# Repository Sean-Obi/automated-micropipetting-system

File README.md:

# Automated Micropipetting System - Gantry + Linear Actuator + Touchscreen

A low-cost, bench-top pipetting robot that lets users with tremors, fatigue or limited upper-limb mobility pipette independently. A modified Ender-3 gantry positions an actuator-driven 3D-printed micropipette over labware, and the whole run is set up from a Nextion touchscreen: pick a source, the destination wells and a volume, then press start.

Built as the Design & Prototyping group project built by nine second-year Molecular Bioengineering students at Imperial College London, supervised by Dr Ian Radcliffe.

> ❗️**Prototype, not a certified lab instrument.** Accuracy was validated on the bench only. Don't use it for regulated or clinical work.

---

## Features
- **3-axis Cartesian gantry** built on a Creality Ender-3 frame, with A4988 drivers and end-stop homing on every axis.
- **Coordinated XY motion** using Bresenham-style interpolation, so both axes arrive together. Z always retracts to a safe height before any travel.
- **Actuator-driven pipette.** A 12 V linear actuator presses the plunger of an open-source, ISO 8655-compliant 3D-printed micropipette.
- **Touchscreen workflow.** Source → wells → volume → start on a 4.3" Nextion HMI, with input validation done on the display.
- **Tactile keypad** (4×3) as an alternative input, plus a **buzzer** for audio feedback at the start and end of each job.
- **Modular PLA base** with a 5×8 tube rack and two beaker slots in fixed, grooved positions.
- **£483.53** material cost, against more than £35,000 for commercial liquid handlers.

---

## Hardware
- Elegoo Mega 2560 R3 (Arduino Mega compatible)
- Creality Ender-3 3D printer (frame, rails, NEMA17 steppers, end-stops, PSU)
- 3 × A4988 stepper driver modules
- Actuonix Linear Actuator Control (LAC) board + linear actuator
- 3D-printed adjustable micropipette (3 mL syringe) + custom pipette/actuator holder
- Nextion NX4827T043 4.3" HMI touchscreen + microSD card
- 4×3 membrane keypad, piezo buzzer
- 3 × LM2596 buck converters, custom interface PCB

Full part list with suppliers and prices: [`hardware/BOM.csv`](hardware/BOM.csv).

### Interface PCB
A 2-layer, 132 × 80 mm board that carries the three A4988 drivers, power inputs and all device connectors, with a 2×14 header to the Mega. KiCad files and Gerbers are in [`hardware/`](hardware/).

> The layout in this repo is a 2026 reconstruction from the report schematic, not the original files sent to JLCPCB. See [`hardware/README.md`](hardware/README.md#board-layout).

### Power
- Mains supplies the Ender-3 PSU (24 W total draw).
- **12 V rail** (via buck converter) powers the LAC board and actuator.
- **5 V rail** (via buck converters) powers the Mega, the A4988 logic and the Nextion.
- A separate buck converter supplies the stepper motor voltage (VMOT).

> Set every LM2596 output with a multimeter **before** connecting anything. They ship at arbitrary voltages.

---

## Pinout / Wiring

| Component | Signal | Mega Pin |
|---|---|---|
| X axis | STEP / DIR / End-stop | **6** / **7** / **5** |
| Y axis | STEP / DIR / End-stop | **9** / **10** / **8** |
| Z axis | STEP / DIR / End-stop | **12** / **13** / **11** |
| LAC board | VC (position signal) | **4** (via R2, with R1 pull-up) |
| Nextion | RX / TX | **TX1 (18)** / **RX1 (19)** |
| Keypad | Rows / columns | **22, 24, 26, 28, 30, 32, 34** |
| Buzzer | + | **2** |
| A4988 | VDD / VMOT | 5V / motor buck output |
| A4988 | SLP ↔ RST | Tied together |
| End-stops | Switch → GND | `INPUT_PULLUP`, triggered = `HIGH` |

> Note: the report's schematic figure shows DIR/STEP swapped, the buzzer on D52 and the Nextion on TX0/RX0. The table above follows the firmware, which is what actually ran. Full schematic: [`hardware/pcb_design.kicad_sch`](hardware/pcb_design.kicad_sch).

---

## Software Requirements
Arduino IDE 1.8+ or Arduino IDE 2.x. **No external libraries** are needed. The sketch only uses the Arduino core (`Serial`, `Serial1`, `tone()`).

For the touchscreen:
- **Nextion Editor** to edit the `.HMI` and compile the `.tft`.

---

## Installation
1. **Clone the repository**
   ```bash
   git clone https://github.com/your-username/automated-micropipetting-system.git
   cd automated-micropipetting-system
   ```
2. Wire the system per the pin table above, and set the A4988 current limits and buck converter voltages.
3. Open `firmware/pipetting_controller/pipetting_controller.ino` in the Arduino IDE.
4. Select **Board → Arduino Mega or Mega 2560** and the correct port.
5. **Verify/Compile**, then **Upload**.
6. Copy the Nextion `.tft` to a FAT32 microSD card, insert it into the display and power it on to flash.
7. (Optional) Open **Tools → Serial Monitor** at **9600 baud** to watch the job logs.

---

## Configuration

Edit these constants near the top of the sketch. All positions are in **steps from home**:

```cpp
const long Z_SAFE_HEIGHT = 1700;   // travel height between positions
const long Z_WORK_HEIGHT = 300;    // tip-in-liquid height
unsigned long stepDelayXY = 1500;  // µs, XY step half-period (lower = faster)
unsigned long stepDelayZ  = 1200;  // µs, Z step half-period
const long MAX_HOMING_STEPS_Z = MAX_BACKWARD_Z + 100;  // Z homing timeout
```

Labware positions come from calibration and must be re-measured if the base changes:
```cpp
Coord wells[]   = { { 890, 500 }, { 940, 500 }, ... };  // 5×8 rack, 50-step pitch
Coord beakers[] = { { 400, 700 }, { 670, 700 } };       // left, right
```

Step resolution (from calibration):
- **X:** ~0.199 mm/step
- **Y:** ~0.205 mm/step
- **Z:** 0.04 mm/step

---

## How It Works

1. **Homing**  
   At power-up, each axis drives toward its end-stop (X → Y → Z) to set an absolute zero. Z then rises to `Z_SAFE_HEIGHT`.

2. **Job Entry**  
   The user steps through the Nextion screens (source type → beaker or input well → output wells → volume). The display checks the inputs, then sends a single packet over `Serial1`, terminated by `#`.

3. **Packet Parsing**  
   `parsePacket()` decodes the ASCII fields (`I=` input well, `O=` output wells) and the 4-byte little-endian fields (`V=` volume, `B=` beaker side, `T=` source type), then plays a confirmation beep.

4. **Execution**  
   The gantry travels to the source and then to each output well in turn. At every stop, `holdZatWorkHeight()` lowers the tip, dwells for 3 s, then retracts. Z always returns to safe height before any XY move.

5. **Return**  
   The head goes back to (0, 0), the end melody plays, and the buffer clears ready for the next job.

---

## Usage

1. Plug in the system and wait for homing to finish.
2. Fill the source beaker or tubes and place them in the marked slots. Fit a fresh tip.
3. On the touchscreen, choose **Beaker** or **Tubes**, then pick the source.
4. Tap the output wells and press **Confirm**.
5. Enter the volume in µL and tap **Start Pipetting**.
6. Two beeps confirm the job, and a melody plays when the head is back home.
7. Remove the tip by hand. There is no auto-eject yet.

Full walkthrough with screenshots: [`docs/user-guide.md`](docs/user-guide.md).

---

## Data Output

### Serial Monitor (9600)
```
Ready to receive Nextion packets...
Input Well: 0
Output Wells: 12,13,14,
Volume: 74
Beaker Side: 1
Source Type: 1
```

### Nextion Packet Format
```
T=<4B> B=<4B> I=<digits> O=<d>,<d>,...; V=<4B> #
```
| Field | Meaning |
|---|---|
| `T` | Source type: 1 = beaker, 2 = tubes |
| `B` | Beaker side: 1 = left, 2 = right |
| `I` | Input well index (0–39) |
| `O` | Output well indices, `;`-terminated |
| `V` | Volume in µL |

### Debug Commands (USB Serial)
| Command | Action |
|---|---|
| `X0` | Re-home X |
| `Y0` | Re-home Y |
| `Z0` | Re-home Z |

---

## Results

- **Volume accuracy:** the pipette alone was calibrated to within ±1% of target. The actuator adds extra uncertainty at system level, and accuracy drops at low volumes.
- **Cross-contamination:** no visible carryover in dye-then-clear runs with tip changes. This was checked by eye only.
- **Gantry:** the step-to-distance response is linear on all axes ([calibration](docs/calibration.md)).
- **User testing (n = 20):**
  - 90% rated lab fit 4–5/5.
  - 75% needed minimal or no instructions.
  - The top requests were a bigger screen, larger touch targets and tactile buttons.

Full evaluation: [`docs/testing.md`](docs/testing.md).

---

## Troubleshooting

- **An axis runs into the frame during homing**
  - Check the end-stop wiring and that it reads `HIGH` when pressed (`LIMIT_PRESSED = HIGH`).
  - XY homing has no step limit. Cut power or press reset if a switch fails.

- **The touchscreen does nothing when you press Start**
  - Nextion TX must go to Mega **RX1 (19)** and Nextion RX to **TX1 (18)**. The crossover matters.
  - Both sides need to be at **9600 baud**.
  - Check that the packet ends with `#`. Watch the Serial Monitor for the `Input Well:` lines.

- **The tip misses the wells**
  - Re-home with `X0` / `Y0` / `Z0`. Position isn't re-homed between jobs, so lost steps accumulate.
  - Re-measure `wells[]` / `beakers[]` if the base has moved.

- **A motor stutters, skips or runs hot**
  - Re-set the A4988 current limit on the trim pot.
  - Increase `stepDelayXY` / `stepDelayZ` to slow the motion.
  - Check that VMOT is present and the driver has airflow or a heatsink.

- **A motor runs backwards**
  - Swap one coil pair (1A/1B) on that driver.

- **The tip doesn't reach the liquid, or it crashes into the tube bottom**
  - Adjust `Z_WORK_HEIGHT`.

---

## Notes & Limitations
- **The volume isn't used by the firmware yet.** `V=` is parsed and logged, but this sketch doesn't generate the actuator PWM. Actuation happens outside this file.
- **16-bit `int` on AVR.** The 4-byte field decoding shifts by 16 and 24 bits, which overflows a 16-bit `int`. It works only because the upper bytes are zero. It should use `int32_t`.
- **Everything is blocking.** There's no cancel or emergency stop mid-job.
- **The keypad isn't implemented here.** It is wired, but this sketch doesn't read it.
- **Tips are ejected manually.** Servo-driven ejection and a tip bin are on the roadmap.
- **Materials.** PLA parts suit prototyping only. The pipette–carriage joint needs a stiffer mount.
- **The volume range is inconsistent across sources.** The spec says 100–1000 µL, the UI guide 10–100 µL, and testing covered 30–100 µL.

More detail: [`firmware/README.md`](firmware/README.md#known-issues).

---

## Project Structure

```
automated-micropipetting-system/
├── firmware/
│   ├── pipetting_controller/
│   │   └── pipetting_controller.ino   # Gantry, homing, Nextion packet parser
│   └── README.md                      # Pinout, protocol, known issues
├── hardware/
│   ├── pcb_design.kicad_pro           # KiCad project
│   ├── pcb_design.kicad_sch           # Schematic
│   ├── pcb_design.kicad_pcb           # Board layout (reconstructed)
│   ├── pcb_design_gerbers.zip         # Gerbers + drill files
│   ├── apms.pretty/                   # Project footprint library
│   ├── pcb_design.pdf                 # Plotted schematic
│   ├── schematic.png                  # Original figure from the report
│   ├── BOM.csv                        # Bill of materials (£483.53)
│   ├── tools/                         # Schematic + board generation scripts
│   └── README.md                      # Power rails, drivers, wiring
├── hmi/
│   └── README.md                      # Nextion screen flow
├── cad/
│   └── README.md                      # SolidWorks parts (base, holders)
├── docs/
│   ├── images/                        # Figures
│   ├── calibration.md                 # Gantry step calibration
│   ├── testing.md                     # Accuracy, contamination, user testing
│   ├── user-guide.md                  # Operating instructions
│   └── final-report.pdf               # Full project report
└── README.md
```

---

## Team
Ben Jones · Jenna du Preez · Kailin Wang · Leonardo Grimaldi · **Sean Obi** · Sheena Ling · Sumaiyah Zaman · Tayeb Tadlaoui · Yasmine Marenzi

### My Contributions (Sean Obi)
- **PCB design.** Designed the custom interface PCB (schematic and layout), manufactured by JLCPCB.
- **Electronics lead.** System wiring and power distribution (12 V actuator rail, 5 V logic), and integration of the drivers, LAC board, keypad, display and buzzer.
- **Firmware.** Co-developed the Arduino controller: homing, XY motion and Nextion packet handling.
- **Gantry.** Assembled the Ender-3 conversion.
- **User testing.** Coordinated the n = 20 study.
- **Final report.** Co-authored it.

---

## Acknowledgements
- Dr Ian Radcliffe (supervisor)
- Imperial Disability Advisory Services and Dr Katherine Dean
- Ms Iris Latham (disability consultant) and Dr Tweety Tang (user-testing sessions)
- Brennan, Bokhari & Eddington: *Open Design 3D-Printable Adjustable Micropipette that Meets the ISO Standard for Accuracy* (Micromachines, 2018)
- Creality Ender-3 · Pololu A4988 · Actuonix LAC · Nextion Editor

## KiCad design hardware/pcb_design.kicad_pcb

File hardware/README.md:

# Hardware

| File | Contents |
|---|---|
| `pcb_design.kicad_pro` | KiCad project (KiCad 7 format; opens in 7, 8 and 9) |
| `pcb_design.kicad_sch` | Schematic |
| `pcb_design.kicad_pcb` | Board layout (reconstructed; see below) |
| `pcb_design_gerbers.zip` | Gerbers and drill files exported from the reconstructed layout |
| `apms.pretty/`, `fp-lib-table` | Project footprint library |
| `pcb_design.pdf` | Plotted schematic |
| `schematic.png` | Original schematic figure from the report (Appendix F) |
| `tools/` | Scripts that generate the schematic and board |
| `BOM.csv` | Bill of materials |

---

## Board Layout

> **Reconstruction.** The original 2025 layout files and the Gerbers sent to JLCPCB aren't in this repo. This layout was rebuilt in 2026 from the report's schematic figure and auto-routed with Freerouting. It is electrically equivalent to the schematic, but it is not the board that was manufactured.

**Board**
- 132 × 80 mm, 2 layers, 1.6 mm thick, with four M3 mounting holes.
- GND pour on both layers.

**Track widths**
| Net class | Nets | Width |
|---|---|---|
| Power | GND, +5V, VMOT, actuator and logic supply | 1.0 mm |
| Motor | Stepper coils | 0.8 mm |
| Signal | Everything else | 0.3 mm |

The board passes KiCad DRC with **0 violations and 0 unconnected pads**.

**On-board**
- 3 × Pololu-format A4988 sockets (X/Y/Z)
- R1/R2 on the LAC control line
- Buzzer
- 3 × 5.08 mm screw terminals for the power inputs

**Connected by header**
- Motors (4-pin) and end-stops (2-pin)
- The three LM2596 modules (IN+, IN−, OUT+, OUT−)
- LAC board, Nextion, legacy I²C LCD (not fitted) and keypad
- A 2×14 **TO MEGA** header carrying every Mega signal

---

## Schematic

The `.kicad_sch` is redrawn from the report figure, with two changes:

1. **It shows all three axes.** The original figure shows one representative driver, motor and end-stop.
2. **Its pin assignments follow the firmware, which is what actually ran.** Where the report figure differs, the firmware wins:

| Signal | Report figure | Schematic / firmware |
|---|---|---|
| X DIR / STEP | D6 / D7 | D7 / D6 |
| Buzzer | D52 | D2 |
| Nextion | TX0 / RX0 | Serial1: TX1 (D18), RX1 (D19) |

Connectivity uses net labels, so every connection is explicit. Every symbol has a footprint from the project library, and **Tools → Update PCB from Schematic** matches the layout.

Before building from these files, check these points against the physical build:

- The values of R1 and R2 on the LAC control line are not given in the report.
- The keypad pin order onto D22–D34 is as drawn in the report.
- `VMOT_GND` and `LAC_V-` are left as separate returns, as drawn. Tie them to GND if the supplies share a ground.

---

## Power

| Rail | Source | Loads |
|---|---|---|
| Mains → 24 V | Ender-3 built-in PSU | Input to buck converters |
| 12 V | Buck converter (LM2596) | Linear actuator via LAC board |
| 5 V | Buck converters (LM2596) | Mega 2560, A4988 logic, Nextion display |
| Motor supply | Buck converter → A4988 VMOT | Stepper coils |

The system draws about 24 W in total.

**Before connecting anything**, set each LM2596 output with a multimeter. The modules ship at arbitrary voltages and will kill the Mega or the display if left unset.

---

## Stepper drivers

There are three A4988 carriers, one each for X, Y and Z (the BOM includes one spare). STEP and DIR go to the Mega (see [firmware pinout](../firmware/README.md#pinout)). Tie SLP and RST together high.

Set the current limit on each driver using the trim pot:

> V_ref = I_max × 8 × R_sense

Set it for the Ender-3's stepper motors (Creality 42-series), and check R_sense on your particular carrier.

---

## Actuator

The linear actuator is driven through an Actuonix Linear Actuator Control (LAC) board. The Mega sends a PWM/RC position signal to the LAC. The LAC closes the position loop and drives the actuator from the 12 V rail. The actuator's rod is mechanically coupled to the pipette plunger, as shown in the [pipette mechanism image](../docs/images/pipette-mechanism.png).

---

## I/O

- **Nextion display:** UART on Serial1 (TX1/RX1), powered from 5 V.
- **Keypad:** 4×3 matrix on D22–D34.
- **Buzzer:** D2.
- **End-stops:** the stock Ender-3 mechanical switches, one per axis.
- **Old I²C LCD:** still shown on the schematic but no longer used.

---

## Bill of materials

See [`BOM.csv`](BOM.csv). The total comes to **£483.53**. The two largest items are the Ender-3 (£139) and the custom PCB (£99.22).

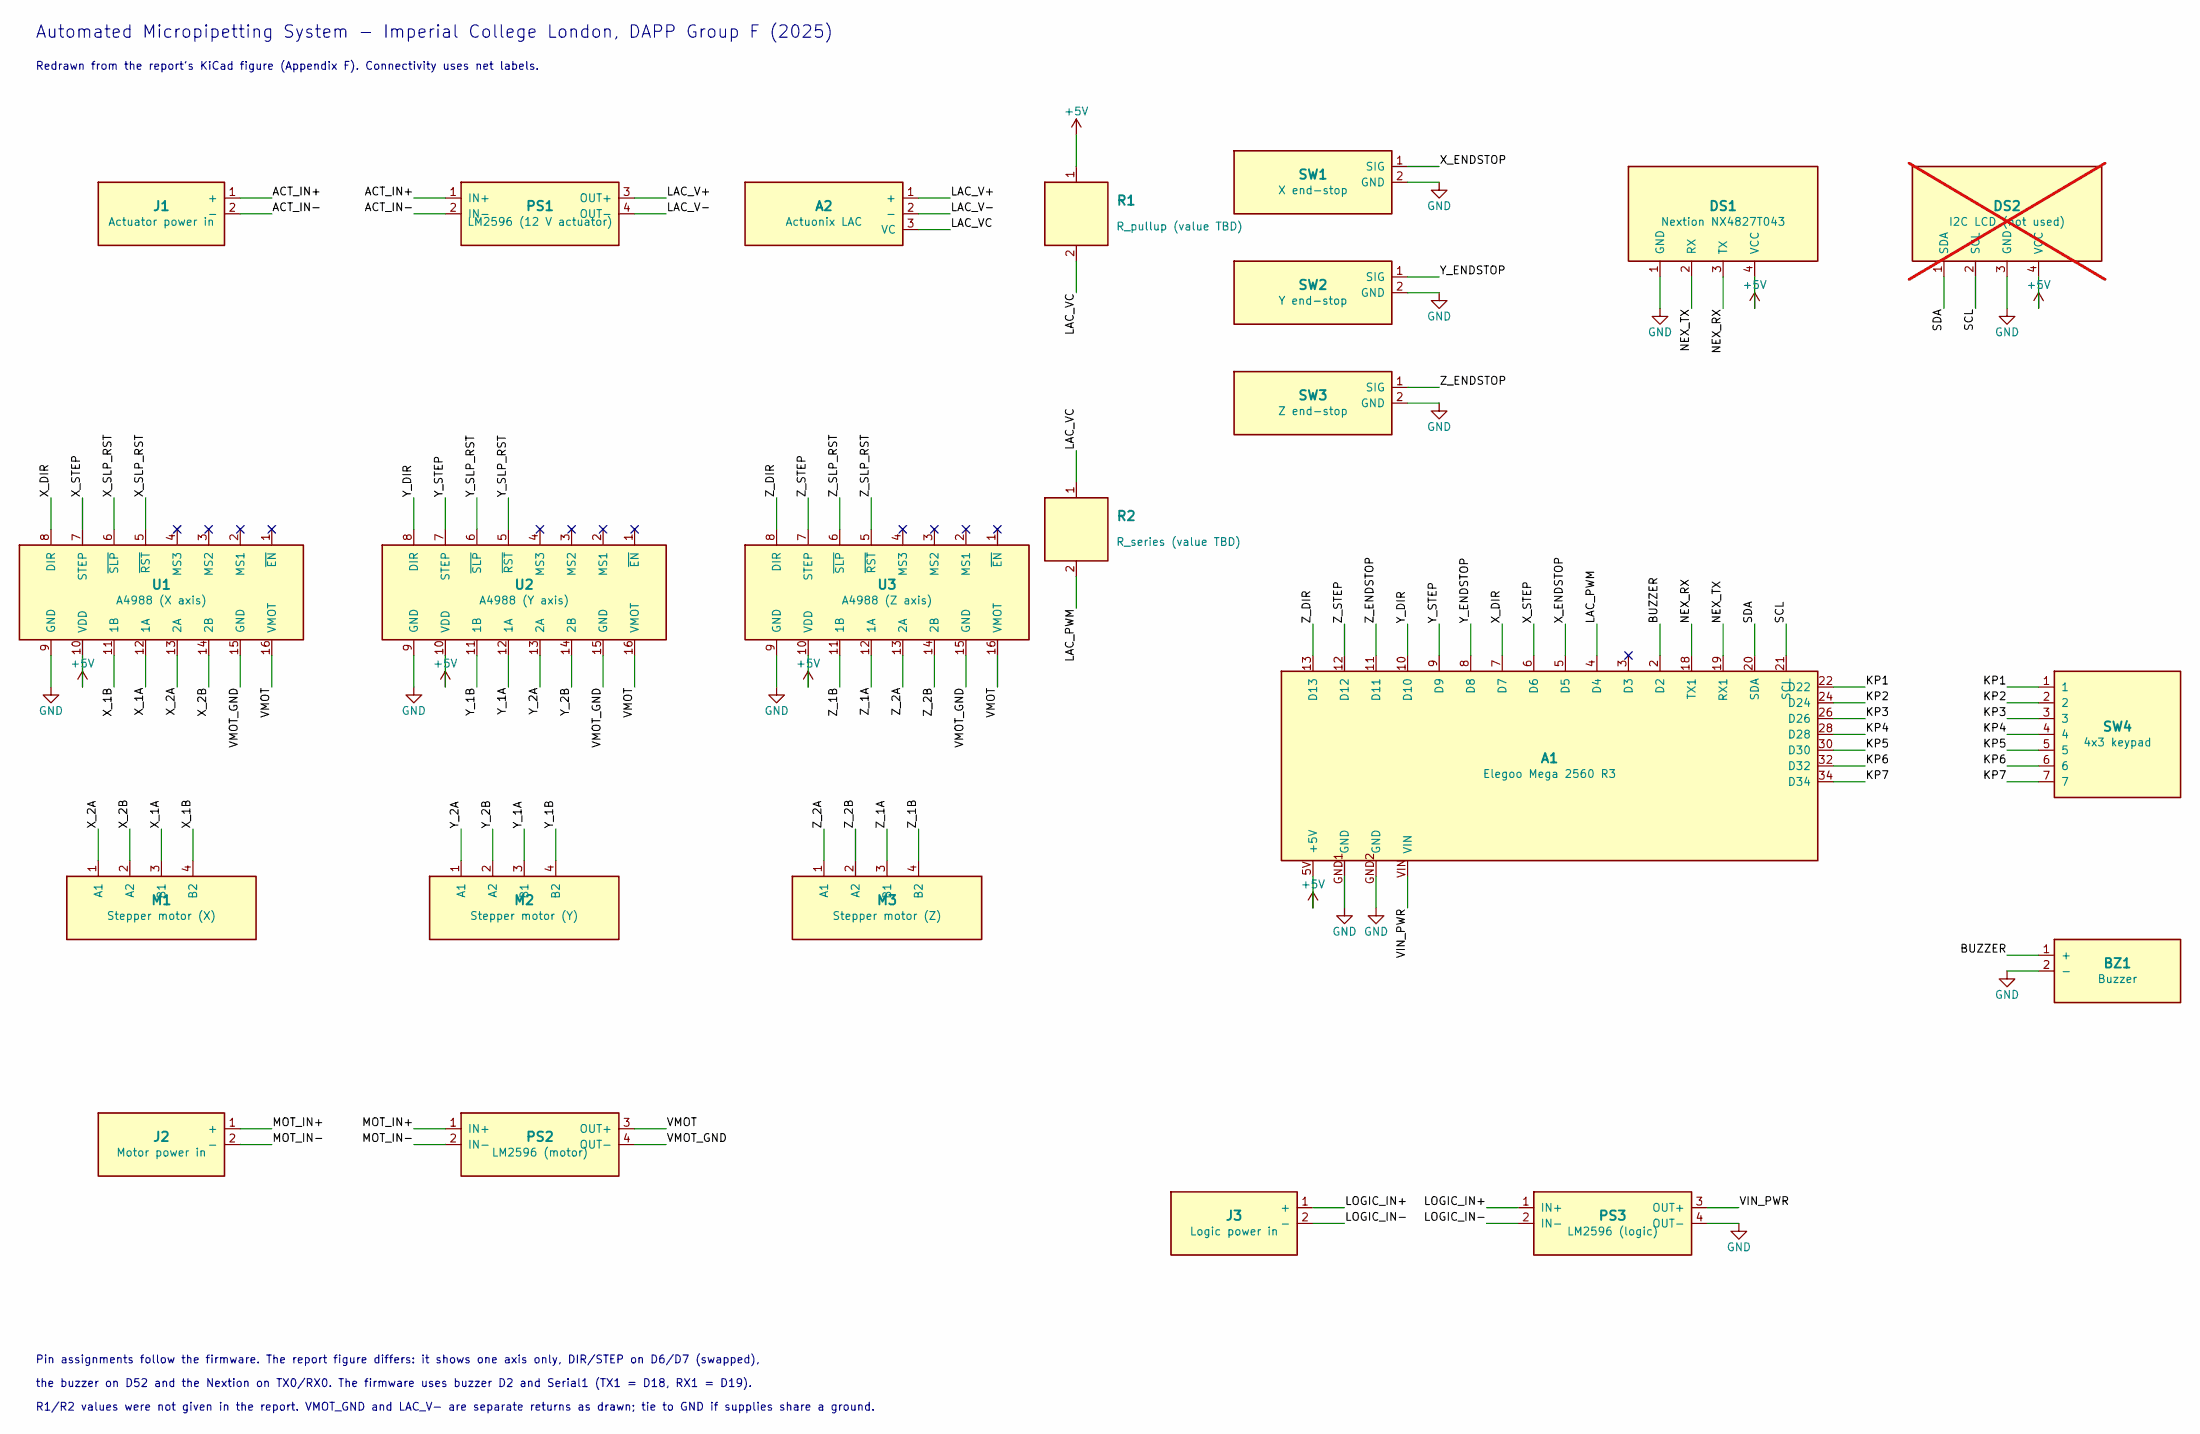
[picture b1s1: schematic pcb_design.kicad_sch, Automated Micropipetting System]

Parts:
A1: Elegoo Mega 2560 R3; Mega2560_Interface_2x14_P2.54mm
A2: Actuonix LAC; PinHeader_1x03_P2.54mm
BZ1: Buzzer; Buzzer_12x9.5RM7.6
DS1: Nextion NX4827T043; PinHeader_1x04_P2.54mm
DS2: I2C LCD (not used); PinHeader_1x04_P2.54mm; not fitted
J1: Actuator power in; TerminalBlock_1x02_P5.08mm
J2: Motor power in; TerminalBlock_1x02_P5.08mm
J3: Logic power in; TerminalBlock_1x02_P5.08mm
M1: Stepper motor (X); PinHeader_1x04_P2.54mm
M2: Stepper motor (Y); PinHeader_1x04_P2.54mm
M3: Stepper motor (Z); PinHeader_1x04_P2.54mm
PS1: LM2596 (12 V actuator); LM2596_Module_Header_1x04
PS2: LM2596 (motor); LM2596_Module_Header_1x04
PS3: LM2596 (logic); LM2596_Module_Header_1x04
R1: R_pullup (value TBD); R_Axial_DIN0207_L6.3mm_P10.16mm
R2: R_series (value TBD); R_Axial_DIN0207_L6.3mm_P10.16mm
SW1: X end-stop; PinHeader_1x02_P2.54mm
SW2: Y end-stop; PinHeader_1x02_P2.54mm
SW3: Z end-stop; PinHeader_1x02_P2.54mm
SW4: 4x3 keypad; PinHeader_1x07_P2.54mm
U1: A4988 (X axis); Pololu_A4988_Carrier_Socket
U2: A4988 (Y axis); Pololu_A4988_Carrier_Socket
U3: A4988 (Z axis); Pololu_A4988_Carrier_Socket

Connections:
+5V: A1.5V (+5V), DS1.4 (VCC), DS2.4 (VCC), R1.1, U1.10 (VDD), U2.10 (VDD), U3.10 (VDD)
/ACT_IN+: J1.1 (+), PS1.1 (IN+)
/ACT_IN-: J1.2 (-), PS1.2 (IN-)
/BUZZER: A1.2 (D2), BZ1.1 (+)
/KP1: A1.22 (D22), SW4.1
/KP2: A1.24 (D24), SW4.2
/KP3: A1.26 (D26), SW4.3
/KP4: A1.28 (D28), SW4.4
/KP5: A1.30 (D30), SW4.5
/KP6: A1.32 (D32), SW4.6
/KP7: A1.34 (D34), SW4.7
/LAC_PWM: A1.4 (D4), R2.2
/LAC_V+: A2.1 (+), PS1.3 (OUT+)
/LAC_V-: A2.2 (-), PS1.4 (OUT-)
/LAC_VC: A2.3 (VC), R1.2, R2.1
/LOGIC_IN+: J3.1 (+), PS3.1 (IN+)
/LOGIC_IN-: J3.2 (-), PS3.2 (IN-)
/MOT_IN+: J2.1 (+), PS2.1 (IN+)
/MOT_IN-: J2.2 (-), PS2.2 (IN-)
/NEX_RX: A1.18 (TX1), DS1.3 (TX)
/NEX_TX: A1.19 (RX1), DS1.2 (RX)
/SCL: A1.21 (SCL), DS2.2 (SCL)
/SDA: A1.20 (SDA), DS2.1 (SDA)
/VIN_PWR: A1.VIN, PS3.3 (OUT+)
/VMOT: PS2.3 (OUT+), U1.16 (VMOT), U2.16 (VMOT), U3.16 (VMOT)
/VMOT_GND: PS2.4 (OUT-), U1.15 (GND), U2.15 (GND), U3.15 (GND)
/X_1A: M1.3 (B1), U1.12 (1A)
/X_1B: M1.4 (B2), U1.11 (1B)
/X_2A: M1.1 (A1), U1.13 (2A)
/X_2B: M1.2 (A2), U1.14 (2B)
/X_DIR: A1.7 (D7), U1.8 (DIR)
/X_ENDSTOP: A1.5 (D5), SW1.1 (SIG)
/X_SLP_RST: U1.5 (~RST), U1.6 (~SLP)
/X_STEP: A1.6 (D6), U1.7 (STEP)
/Y_1A: M2.3 (B1), U2.12 (1A)
/Y_1B: M2.4 (B2), U2.11 (1B)
/Y_2A: M2.1 (A1), U2.13 (2A)
/Y_2B: M2.2 (A2), U2.14 (2B)
/Y_DIR: A1.10 (D10), U2.8 (DIR)
/Y_ENDSTOP: A1.8 (D8), SW2.1 (SIG)
/Y_SLP_RST: U2.5 (~RST), U2.6 (~SLP)
/Y_STEP: A1.9 (D9), U2.7 (STEP)
/Z_1A: M3.3 (B1), U3.12 (1A)
/Z_1B: M3.4 (B2), U3.11 (1B)
/Z_2A: M3.1 (A1), U3.13 (2A)
/Z_2B: M3.2 (A2), U3.14 (2B)
/Z_DIR: A1.13 (D13), U3.8 (DIR)
/Z_ENDSTOP: A1.11 (D11), SW3.1 (SIG)
/Z_SLP_RST: U3.5 (~RST), U3.6 (~SLP)
/Z_STEP: A1.12 (D12), U3.7 (STEP)
GND: A1.GND1 (GND), A1.GND2 (GND), BZ1.2 (-), DS1.1 (GND), DS2.3 (GND), PS3.4 (OUT-), SW1.2 (GND), SW2.2 (GND), SW3.2 (GND), U1.9 (GND), U2.9 (GND), U3.9 (GND)

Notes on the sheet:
Automated Micropipetting System - Imperial College London, DAPP Group F (2025)
Redrawn from the report's KiCad figure (Appendix F). Connectivity uses net labels.
Pin assignments follow the firmware. The report figure differs: it shows one axis only, DIR/STEP on D6/D7 (swapped),
the buzzer on D52 and the Nextion on TX0/RX0. The firmware uses buzzer D2 and Serial1 (TX1 = D18, RX1 = D19).
R1/R2 values were not given in the report. VMOT_GND and LAC_V- are separate returns as drawn; tie to GND if supplies share a ground.

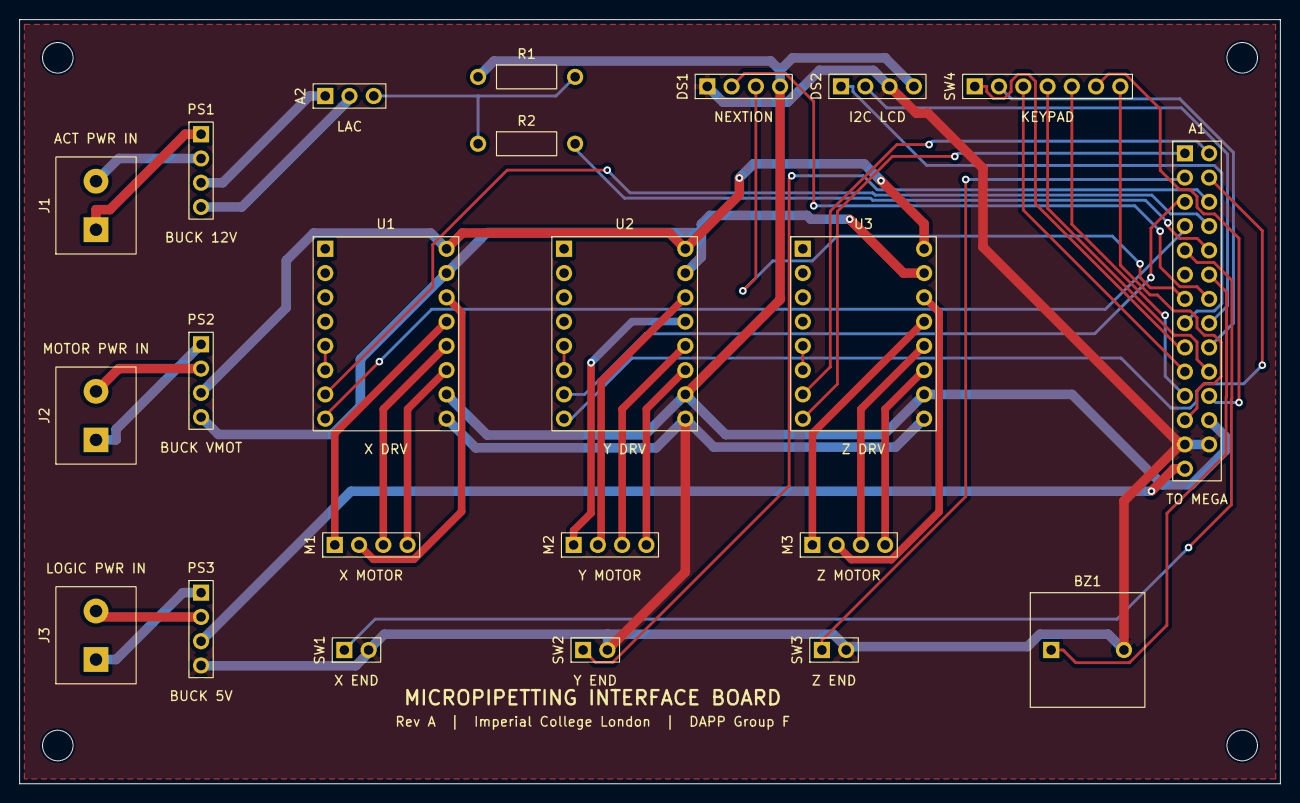
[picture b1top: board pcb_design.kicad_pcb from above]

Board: 2 copper layers, 132.0 x 80.0 mm, 27 parts (0 on the bottom side), 51 nets.

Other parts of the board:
H1, H2, H3, H4: MountingHole_3.2mm_M3
